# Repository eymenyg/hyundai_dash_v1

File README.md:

# How to use the software
1. Download the repository by clicking the green **Code** button and then **Download ZIP**
    - For BeamNG.drive, copy the **hyundai_dash_v1_bng_(latest-date).zip** file under the **BeamNG** folder to **C:\Users\\*username*\\AppData\Local\BeamNG\BeamNG.drive\current\mods**
    - For ATS/ETS2, install [ETS2 Telemetry Server](https://github.com/Funbit/ets2-telemetry-server?tab=readme-ov-file#installation) and run it
        - From the **Network Interfaces** menu, select **Loopback Pseudo-Interface 1**. The server IP should be **127.0.0.1**
    - For Assetto Corsa, you will need [Content Manager](https://acstuff.club/app/) and [Custom Shaders Patch](https://acstuff.club/patch/). Install the **hyundaidashv1_ac_(latest-date).zip** under the **Assetto Corsa** folder through Content Manager or extract the zip to the game folder.
2. Download **hdv1_gui.exe** from the **Releases** section on the right side of the page
3. Open Device Manager in Windows, go to **Ports (COM & LPT)**, check which port is the Arduino on. You can determine it
    by unplugging and plugging it back and observing the window.
3. Run **hdv1_gui.exe**, select the game and the port. You can also build the executable from the scripts by yourself.

# (Optional) Building the executable
1. Install Python if not installed: [Python.org](https://www.python.org). Make sure to add Python to PATH when asked.
2. Install the pyserial and pyinstaller packages by opening a cmd/PowerShell/Terminal window and running the command: `pip install pyserial pyinstaller requests`
3. Navigate to the *scripts* folder and run `pyinstaller --onefile --windowed hdv1_gui.py`. The hdv1_gui.exe will be under the *dist* folder.

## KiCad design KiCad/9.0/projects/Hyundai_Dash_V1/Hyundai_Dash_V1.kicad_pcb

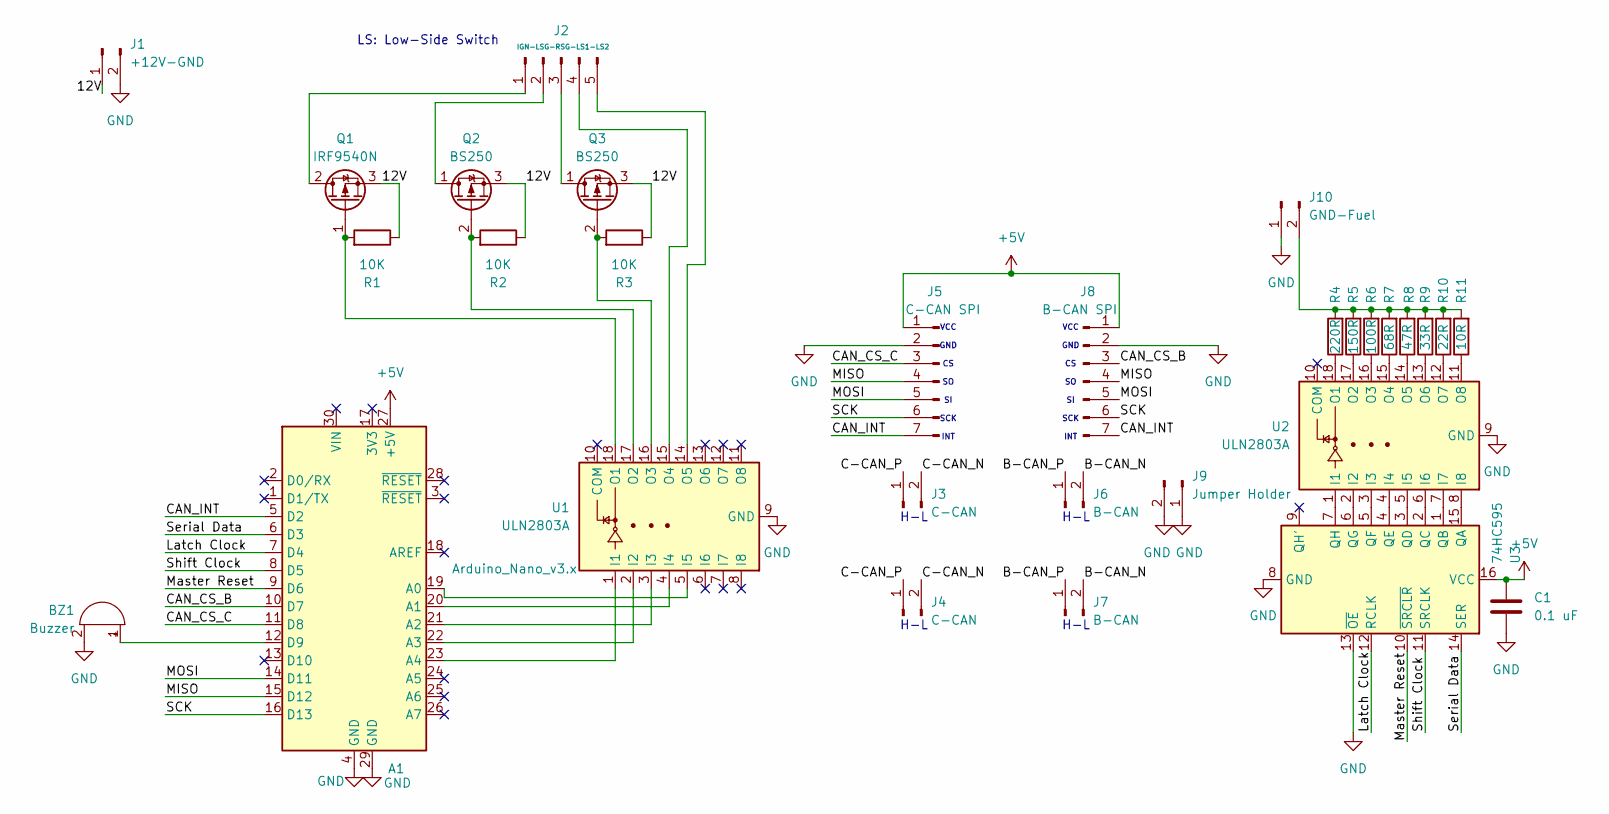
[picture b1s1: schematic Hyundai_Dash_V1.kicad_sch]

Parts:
A1: Arduino_Nano_v3.x; Arduino_Nano
BZ1: Buzzer; Buzzer_12x9.5RM7.6
C1: 0.1 uF; C_0603_1608Metric
J1: +12V-GND; JST_XH_B2B-XH-A_1x02_P2.50mm_Vertical
J2: IGN-LSG-RSG-LS1-LS2; JST_XH_B5B-XH-A_1x05_P2.50mm_Vertical
J3: C-CAN; PinSocket_1x02_P2.54mm_Vertical
J4: C-CAN; JST_XH_B2B-XH-A_1x02_P2.50mm_Vertical
J5: C-CAN SPI; PinSocket_1x07_P2.54mm_Vertical
J6: B-CAN; PinSocket_1x02_P2.54mm_Vertical
J7: B-CAN; JST_XH_B2B-XH-A_1x02_P2.50mm_Vertical
J8: B-CAN SPI; PinSocket_1x07_P2.54mm_Vertical
J9: Jumper Holder; PinHeader_1x02_P2.54mm_Vertical
J10: GND-Fuel; JST_XH_B2B-XH-A_1x02_P2.50mm_Vertical
Q1: IRF9540N; TO-220-3_Vertical
Q2, Q3: BS250; TO-92_Inline
R1, R2, R3: 10K; R_0603_1608Metric
R4: 220R; R_2512_6332Metric
R5: 150R; R_2512_6332Metric
R6: 100R; R_2512_6332Metric
R7: 68R; R_2512_6332Metric
R8: 47R; R_2512_6332Metric
R9: 33R; R_2512_6332Metric
R10: 22R; R_2512_6332Metric
R11: 10R; R_2512_6332Metric
U1, U2: ULN2803A; DIP-18_W7.62mm_Socket
U3: 74HC595; DIP-16_W7.62mm_Socket

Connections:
+5V: A1.27 (+5V), C1.1, J5.1, J8.1, U3.16 (VCC)
/12V: J1.1, Q1.3 (S), Q2.3 (S), Q3.3 (S), R1.1, R2.1, R3.1
/B-CAN_N: J6.2, J7.2
/B-CAN_P: J6.1, J7.1
/C-CAN_N: J3.2, J4.2
/C-CAN_P: J3.1, J4.1
/CAN_CS_B: A1.10 (D7), J8.3
/CAN_CS_C: A1.11 (D8), J5.3
/CAN_INT: A1.5 (D2), J5.7, J8.7
/Latch Clock: A1.7 (D4), U3.12 (RCLK)
/MISO: A1.15 (D12), J5.4, J8.4
/MOSI: A1.14 (D11), J5.5, J8.5
/Master Reset: A1.9 (D6), U3.10 (~SRCLR)
/SCK: A1.16 (D13), J5.6, J8.6
/Serial Data: A1.6 (D3), U3.14 (SER)
/Shift Clock: A1.8 (D5), U3.11 (SRCLK)
GND: A1.4 (GND), A1.29 (GND), BZ1.2 (-), C1.2, J1.2, J5.2, J8.2, J9.1, J9.2, J10.1, U1.9 (GND), U2.9 (GND), U3.8 (GND), U3.13 (~OE)
unnamed: A1.19 (A0), U1.5 (I5)
unnamed: A1.20 (A1), U1.4 (I4)
unnamed: A1.21 (A2), U1.3 (I3)
unnamed: A1.22 (A3), U1.2 (I2)
unnamed: A1.23 (A4), U1.1 (I1)
unnamed: A1.12 (D9), BZ1.1 (+)
unnamed: J2.1, Q1.2 (D)
unnamed: J2.2, Q2.1 (D)
unnamed: J2.3, Q3.1 (D)
unnamed: J2.4, U1.15 (O4)
unnamed: J2.5, U1.14 (O5)
unnamed: J10.2, R4.2, R5.2, R6.2, R7.2, R8.2, R9.2, R10.2, R11.2
unnamed: Q1.1 (G), R1.2, U1.18 (O1)
unnamed: Q2.2 (G), R2.2, U1.17 (O2)
unnamed: Q3.2 (G), R3.2, U1.16 (O3)
unnamed: U2.1 (I1), U3.7 (QH)
unnamed: U2.2 (I2), U3.6 (QG)
unnamed: U2.3 (I3), U3.5 (QF)
unnamed: U2.4 (I4), U3.4 (QE)
unnamed: U2.5 (I5), U3.3 (QD)
unnamed: U2.6 (I6), U3.2 (QC)
unnamed: U2.7 (I7), U3.1 (QB)
unnamed: U2.8 (I8), U3.15 (QA)
unnamed: R4.1, U2.18 (O1)
unnamed: R5.1, U2.17 (O2)
unnamed: R6.1, U2.16 (O3)
unnamed: R7.1, U2.15 (O4)
unnamed: R8.1, U2.14 (O5)
unnamed: R9.1, U2.13 (O6)
unnamed: R10.1, U2.12 (O7)
unnamed: R11.1, U2.11 (O8)

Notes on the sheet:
LS: Low-Side Switch
H-L
VCC GND CS SO SI SCK INT

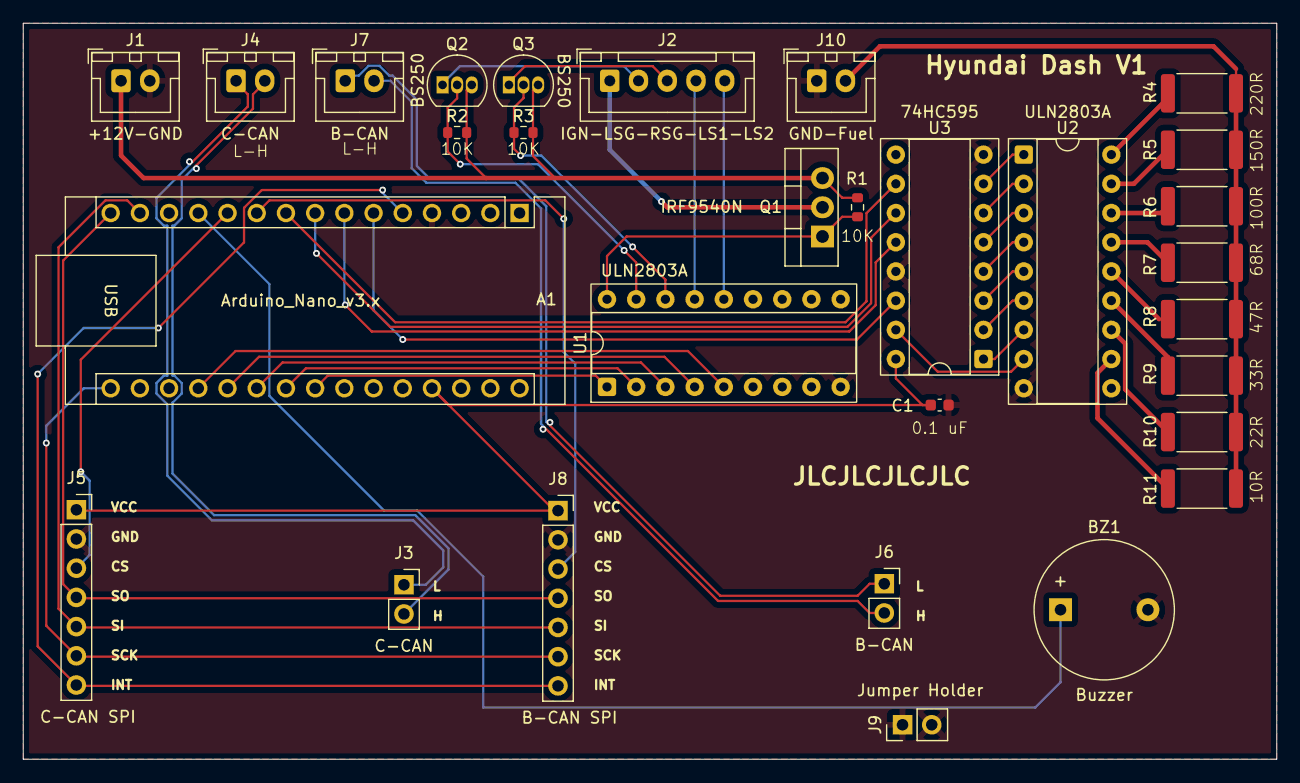
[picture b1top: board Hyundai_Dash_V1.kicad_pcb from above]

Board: 2 copper layers, 109.0 x 64.0 mm, 30 parts (0 on the bottom side), 48 nets.

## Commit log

2026-02-02 init repo with current code
2026-02-02 add KiCad files
2026-02-03 add BeamNG mod zip
2026-02-03 add BeamNG readme
2026-02-03 add PATH reminder to BeamNG readme
2026-02-03 add ETS2 readme
2026-02-04 fix broken beamng mod zip
2026-02-04 BeamNG: set UDP port as 9532 to avoid conflict with SimHub's 9999
2026-02-06 clean up old scripts and add new scripts
2026-02-06 clarify README.md
2026-02-07 Soul_PS: set HS2Role to SRS
2026-02-28 BeamNG: cleanup code, rename mod, restructure dirs
2026-02-28 add RPM scaling option
2026-02-28 add support for Assetto Corsa
2026-02-28 BeamNG: rename mod zip file to prevent mix ups
2026-02-28 Update README.md
    add "requests" as a dependency for building
2026-02-28 README: update AC instructions
2026-02-28 Update README.md
    Custom Shaders Patch*
2026-02-28 reset Arduino on script stop to turn off the cluster
